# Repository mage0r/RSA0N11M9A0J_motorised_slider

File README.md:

RSA0N11M9A0J_motorised_slider
=============

This project drives a model RSA0N11M9A0J motorised slider using a common L9110 H-Bridge driver.

It also allows using the built in capacitive sensor to prevent the motor from fighting manual movement.

There has three sections, a kicad circuit diagram, an arduino sketch using the capacitive touch library and lastly a few photos of it in action.

The specifications for the slider are available at (http://www.alps.com/WebObjects/catalog.woa/E/HTML/Potentiometer/SlidePotentiometers/RSN1M/RSA0N11M9A0J.html).  These sliders were salvaged from a Yamaha M7 Audio Mixer (http://www.yamahaproaudio.com/global/en/products/mixers/m7cl/index.jsp) while it was being refurbished.

There are two sketches in the arduino directory.  One for the attiny controller, another one with a basic i2c master for controlling the slaves.  Each sketch includes a list of required libraries.

Improvements and changes cheerfully accepted.

(http://youtu.be/SSg5tWOZ5IY "ATtiny Slider Driver - Version 2")

(http://youtu.be/dVUSyDtoAqI "ATtiny 84 Motorised Slider - Version 3 ")

CREDITS
------------
This board was designed by John Spencer - john.spencer.9000@gmail.com - https://github.com/mage0r

SPECIAL THANKS
------------
To the creators and maintainers of the KiCAD open-source EDA suite.

To the HackMelbourne (CCHS, http://hackmelbourne.org) community of Melbourne, Australia.

To all other open-source developers whose countless hours supported every other aspect of this design.

To Andy Gelme for feature creeping an attiny in the design.

Extra thanks to Bob Powers (@rdpowers) because I copied his README.md almost verbatim...

DISTRIBUTION
------------
The specific terms of distribution of this project are governed by the
license referenced below. Please contact the copyright owner if you wish to modify the board for distribution. Please utilize this design for personal or research projects. Please acknowledge all contributors.

LICENSE
-------
Licensed under the TAPR Open Hardware License (www.tapr.org/OHL).
The "license" sub-folder also contains a copy of this license in plain text format.

Copyright John Spencer 2014
john.spencer.9000@gmail.com

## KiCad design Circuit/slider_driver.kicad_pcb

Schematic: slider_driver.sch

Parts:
AFF1: 3X7SEGMENTS_1
C1, C3, C4: 0.1uf
C2, C5: 10uf
D1: LED
IC1: ATTINY84A-SS; SO14
K1: Neopixel
K2: PWR
P1, P2: 5_PIN_SOCKET
P3: ISCP
P4: Bridge
R1: 28
R2, R4, R5: 10k
R3: 1M
R15: 1K
U1: MAX7219
U2: RSA0N11M9A0J
U3: L9110

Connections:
+5V: C1.1, C2.1, C4.1, C5.1, IC1.1 (VCC), K1.1, K2.1, P1.1, P2.1, P3.2 (VCC), P4.1, R1.2, R2.1, R4.1, R5.2, R15.1, U1.19 (VCC), U2.1 (+V)
+12V: K2.3, P4.2 (PM), U3.2 (VCC), U3.3 (VCC)
GND: C1.2, C2.2, C4.2, C5.2, D1.2 (K), IC1.14 (GND), K1.3, K2.2 (PM), P1.2, P2.2, P3.6 (GND), U1.4 (GND), U1.9 (GND), U2.3 (GND), U3.5 (GND), U3.8 (GND)
IA: IC1.6 ((PCINT7/ICP/OC0B/ADC7)PA7), R5.1, U3.6 (IA)
IB: IC1.5 ((PCINT10/CKOUT/OC0A/INT0)PB2), R4.2, U3.7 (IB)
MISO: IC1.8 ((PCINT5/DO/MISO/OC1B/ADC5)PA5), P3.1 (MISO), R3.1
MOSI: IC1.7 ((PCINT6/SDA/DI/MOSI/OC1A/ADC6)PA6), P3.4 (MOSI)
Motor_1: C3.2, U2.A (Motor_1), U3.4 (OB)
Motor_2: C3.1, U2.B (Motor_2), U3.1 (OA)
unnamed: P1.5, U1.13 (CLK)
unnamed: R1.1, U1.18 (ISET)
unnamed: AFF1.5, U1.17 (SEG_G)
unnamed: AFF1.7, U1.16 (SEG_B)
unnamed: AFF1.10, U1.15 (SEG_F)
unnamed: AFF1.11, U1.14 (SEG_A)
unnamed: AFF1.2, U1.23 (SEG_D)
unnamed: AFF1.3, U1.22 (SEG_DP)
unnamed: P1.4, U1.12 (LOAD)
unnamed: AFF1.1, U1.21 (SEG_E)
unnamed: AFF1.4, U1.20 (SEG_C)
unnamed: AFF1.12, U1.2 (DIG0)
unnamed: AFF1.9, U1.11 (DIG1)
unnamed: AFF1.8, U1.6 (DIG2)
unnamed: P1.3, U1.1 (DIN)
unnamed: IC1.2 ((PCINT8/CLKI/XTAL1)PB0), K1.2 (PM)
unnamed: D1.1 (A), R15.2
RCLK: IC1.3 ((PCINT9/XTAL2)PB1), P2.5
RESET: IC1.4 ((PCINT11/dW/~RESET~)PB3), P3.5 (RST), R2.2
Receive: IC1.12 ((PCINT1/AIN0/ADC1)PA1), R3.2, U2.T (Touch)
SCK: IC1.9 ((PCINT4/USCK/SCL/T1/ADC4)PA4), P3.3 (SCK)
SER: IC1.11 ((PCINT2/AIN1/ADC2)PA2), P2.3
SRCLK: IC1.10 ((PCINT3/T0/ADC3)PA3), P2.4
Wiper: IC1.13 ((PCINT0/AREF/ADC0)PA0), U2.2 (Wiper)

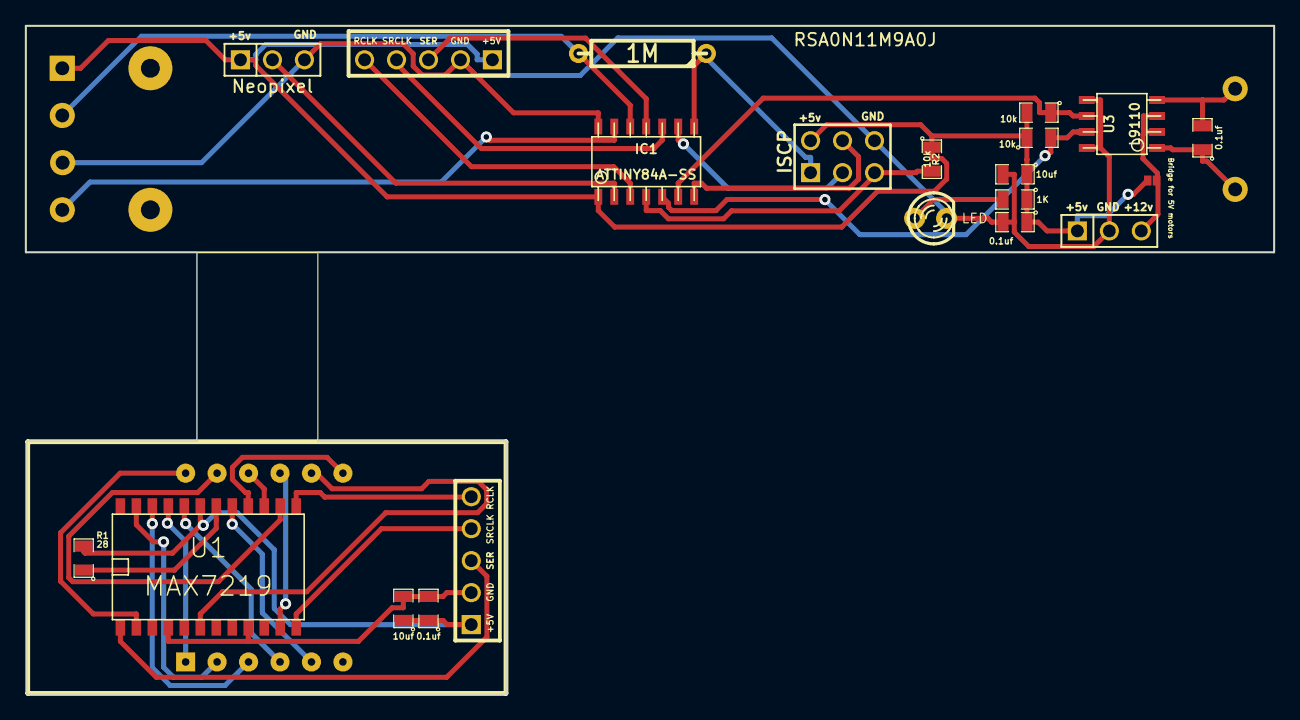
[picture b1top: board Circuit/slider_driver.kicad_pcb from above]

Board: 2 copper layers, 99.2 x 53.1 mm, 23 parts (0 on the bottom side), 33 nets.

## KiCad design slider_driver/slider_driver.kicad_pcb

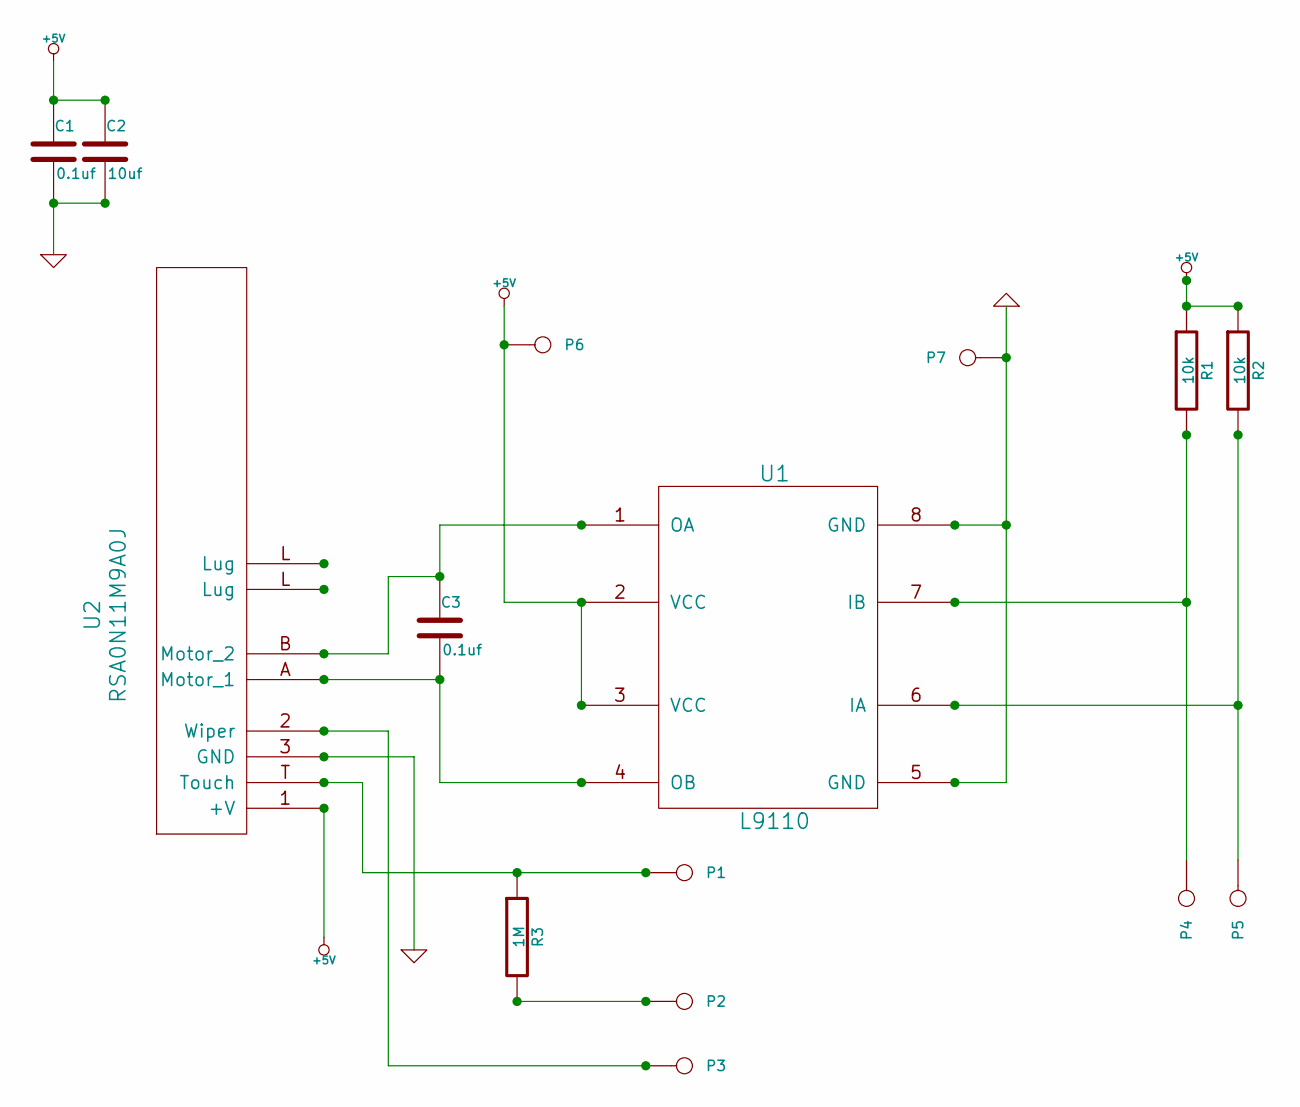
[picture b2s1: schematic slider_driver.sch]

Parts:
C1, C3: 0.1uf
C2: 10uf
P1: TOUCH1
P2: TOUCH2
P3: WIPER
P4: IB
P5: IA
P6: +V
P7: GND
R1, R2: 10k
R3: 1M
U1: L9110
U2: RSA0N11M9A0J

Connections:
+5V: C1.1, C2.1, P6.1, R1.1, R2.1, U1.2 (VCC), U1.3 (VCC), U2.1 (+V)
GND: C1.2, C2.2, P7.1, U1.5 (GND), U1.8 (GND), U2.3 (GND)
unnamed: C3.2, U1.4 (OB), U2.A (Motor_1)
unnamed: P5.1, R2.2, U1.6 (IA)
unnamed: P4.1, R1.2, U1.7 (IB)
unnamed: C3.1, U1.1 (OA), U2.B (Motor_2)
unnamed: P3.1, U2.2 (Wiper)
unnamed: P2.1, R3.2
unnamed: P1.1, R3.1, U2.T (Touch)

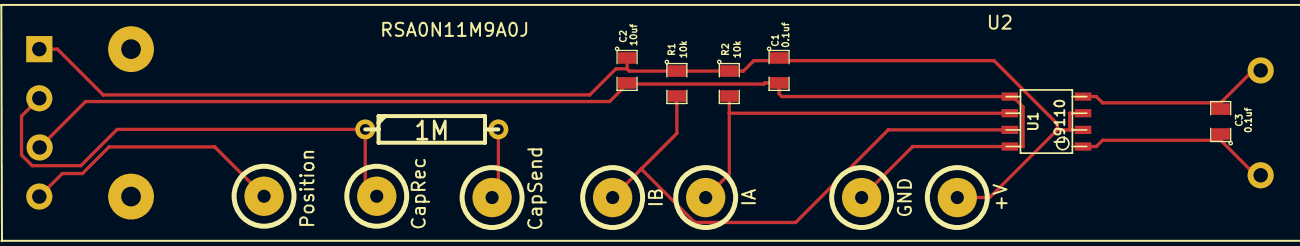
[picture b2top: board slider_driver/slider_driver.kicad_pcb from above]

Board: 2 copper layers, 15 parts (0 on the bottom side), 9 nets.

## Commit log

2014-01-23 Added readme, license and photo
2014-01-23 changes to readme
2014-01-23 Added arduino code
2014-01-23 trying to get the readme right.
2014-01-23 plain link it is then!
2014-01-23 kicad files uploaded
2014-01-26 added attiny to board
    Bit of a feature creep here. The board is now it's own little self
    contained unit that can be accessed using i2c.
2014-01-26 added png's of the board
2014-02-25 changed directory structure
2014-03-02 fixed pin for iscp port
    Total screw up there.
2014-03-08 experimental motorslider
2014-03-09 Code now flashes neopixels.
2014-03-09 updated photo
2014-03-09 typo
2014-03-12 Extra pins Re Bug #3
2014-03-15 typo in i2c pin name
2014-03-19 i2c support added into arduino
    No idea what I changed in the pcb :)
2014-03-19 Added where the sliders were salvaged from
2014-03-20 Added extra youtube link to readme
2014-04-03 These files aren't meant to be there....
    They're all out of date anyway.
2014-04-03 ignoring gerbers and zips
2015-06-29 Updated board
2015-06-29 Updated board to support max chip
2015-07-28 Adaption to make fab people happy.
2015-10-24 testing some stuff
2016-09-08 Some changes that I guess were important at some point
